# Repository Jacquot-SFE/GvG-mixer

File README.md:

The Gort Vs Goom IEM Mixer.
========================================

Read more about it in [my blog post](https://www.sparkfun.com/news/2352)

Repository Contents
-------------------

* **/Datasheets** - Data sheets for the ICs & other components.
* **/Eagle** - PCB files
* **/Spice** - Simulations of the baxandall and peak hold circuits.
* **/Block-diagram** - Poorly named.  Various vector art, including a block diagram, and panel files.

Documentation
----

Ideas mainly pulled from Doug Self's _Small Signal Audio Design_ book, with other input from datasheets and appnotes from THAT, Jensen, and Nat Semi.

License Information
-------------------

This product is _**open source**_!

Please review the LICENSE.md file for license information.

If you have any questions or concerns on licensing, please contact techsupport@sparkfun.com.

Distributed as-is; no warranty is given.

- Your friends at SparkFun.

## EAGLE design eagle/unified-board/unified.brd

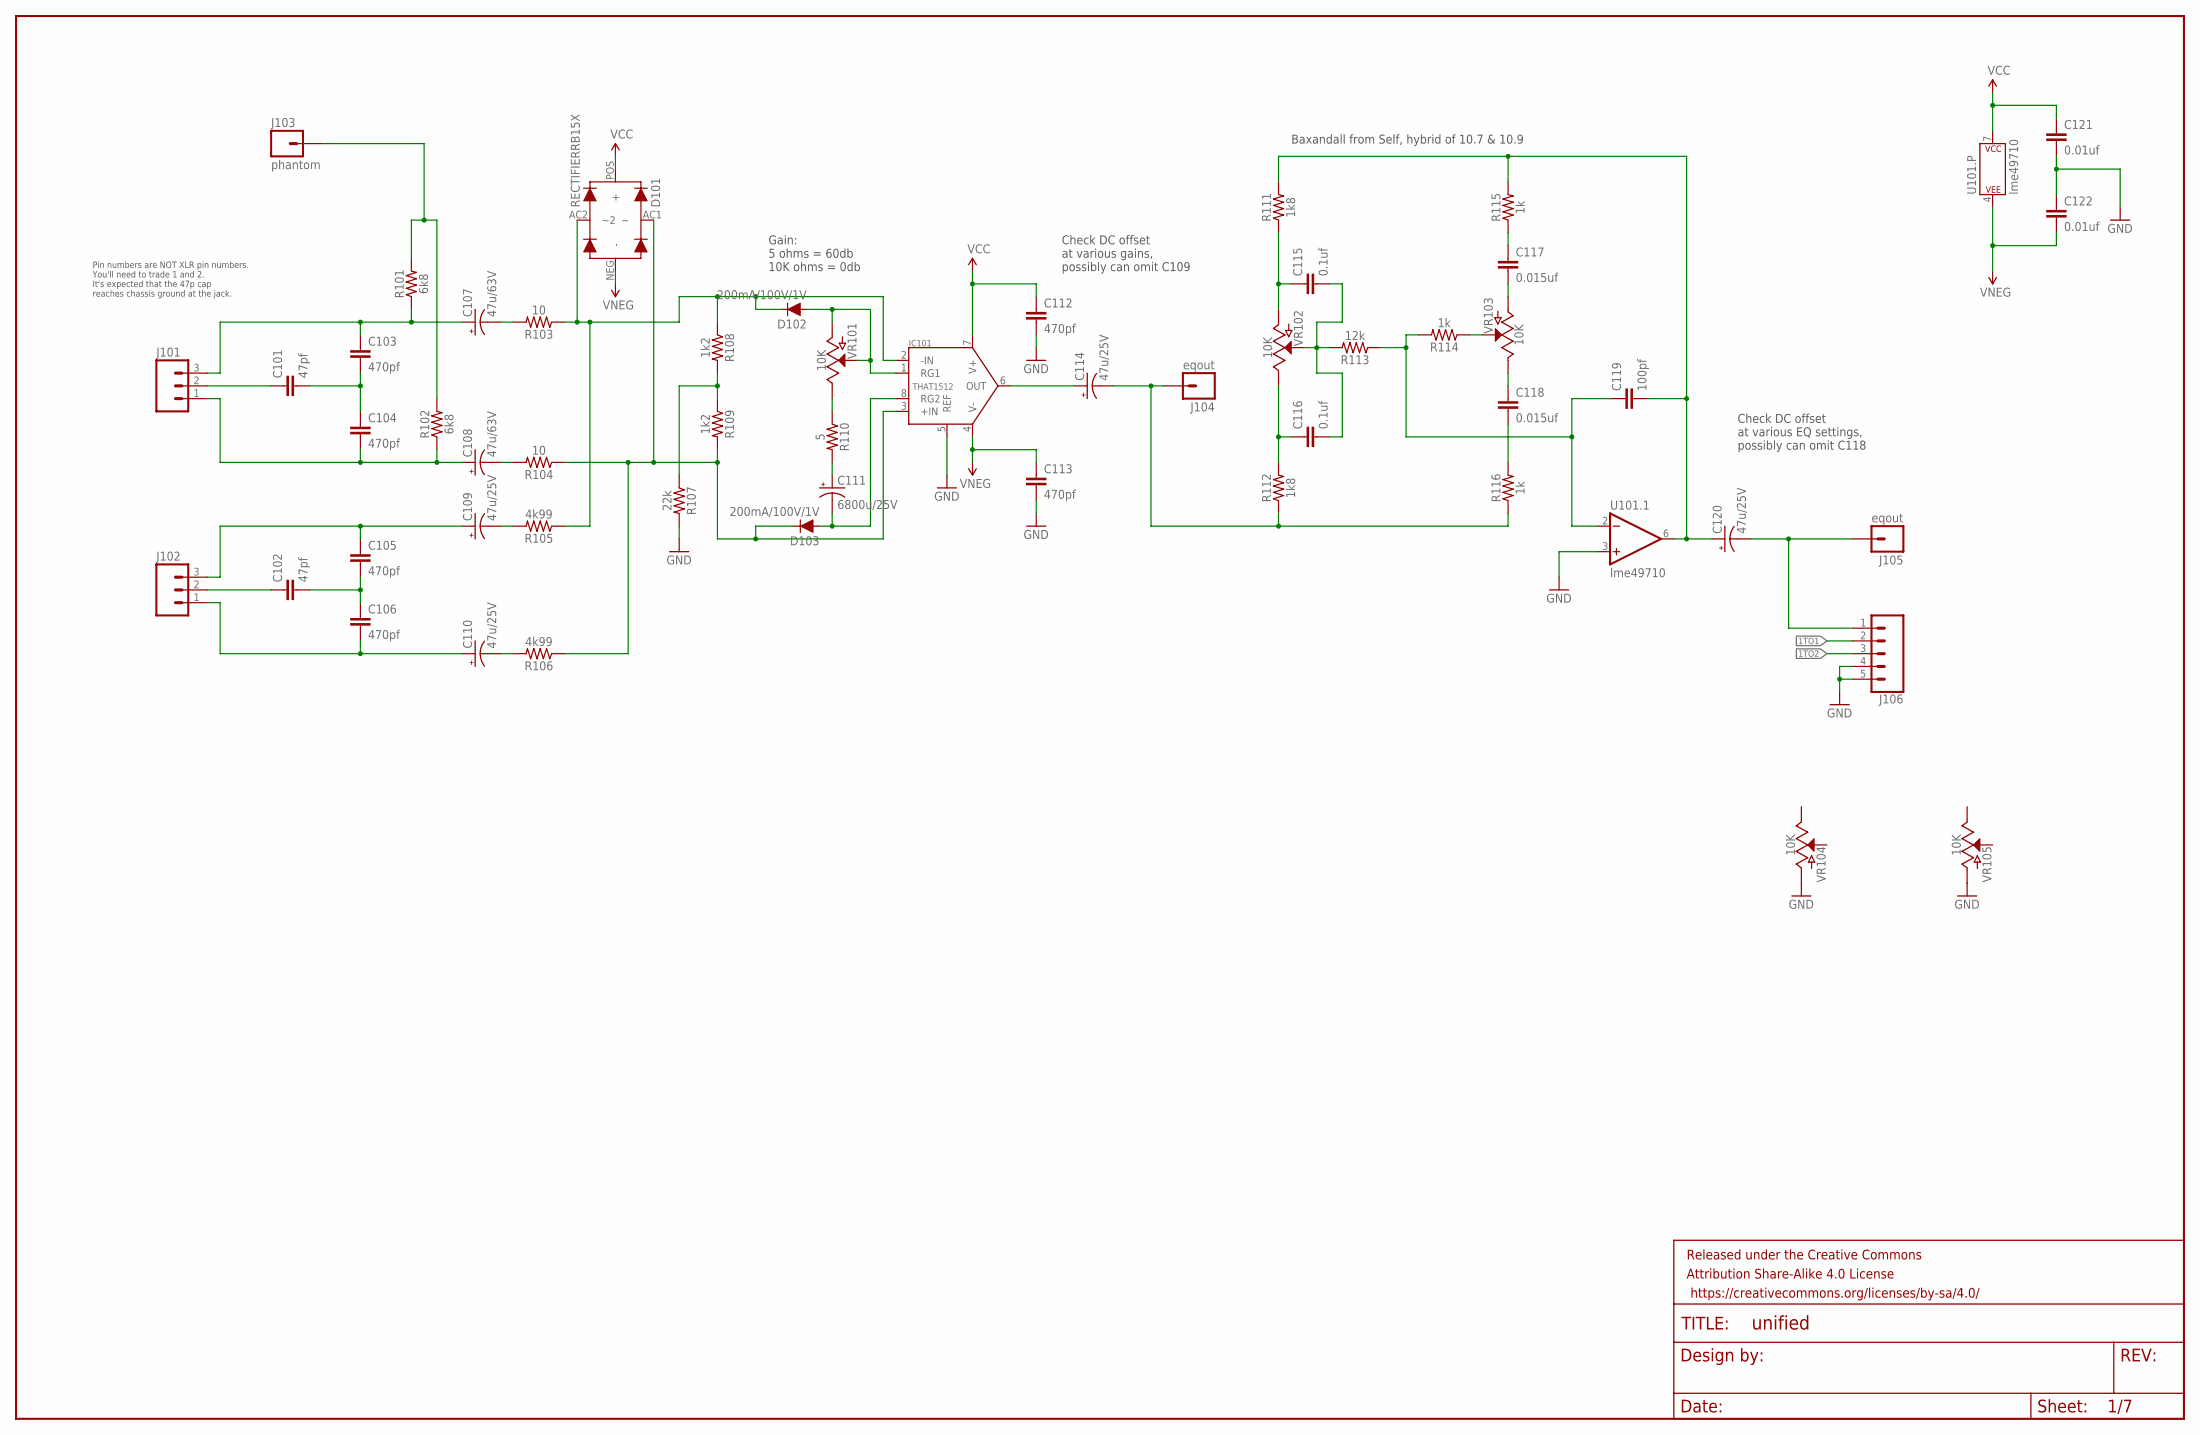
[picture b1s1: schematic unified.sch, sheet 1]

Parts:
C101, C102: 47pf; CAP-KEMET-GM-2.54LS
C103, C104, C105, C106, C112, C113: 470pf; CAP-KEMET-GM-2.54LS
C107, C108: 47u/63V; CAP-PANA-2LS-6DIAM
C109, C110, C114, C120: 47u/25V; CAP-PANA-2LS-5DIAM
C111: 6800u/25V; CAP-PANA-5LS-12.5DIAM
C115, C116: 0.1uf; WIMA-MKS2-2.5X7.2
C117, C118: 0.015uf; WIMA-MKS2-2.5X7.2
C119: 100pf; CAP-KEMET-GM-2.54LS
C121, C122: 0.01uf; WIMA-MKS2-2.5X7.2
D101: RECTIFIERRB15X; SM-RECTIFIER
D102, D103: 200mA/100V/1V; DIODE-1N4148
FRAME101: FRAME-LEDGER; CREATIVE_COMMONS
IC101: THAT1512; DIP08-KIT
J101, J102: M031X03_NO_SILK; 1X03_NO_SILK@1
J103: phantom; 1X01NS-KIT
J104, J105: eqout; 1X01NS-KIT
J106: CONN_05PTH_LONGPADS; 1X05_LONGPADS
R101, R102: 6k8; AXIAL-0.3
R103, R104: 10; AXIAL-0.3
R105, R106: 4k99; AXIAL-0.3
R107: 22k; AXIAL-0.3
R108, R109: 1k2; AXIAL-0.3
R110: 5; AXIAL-0.3
R111, R112: 1k8; AXIAL-0.3
R113: 12k; AXIAL-0.3
R114, R115, R116: 1k; AXIAL-0.3
U101: lme49710; DIP08-KIT
VR101: 10K; ROT-SW-POT
VR102, VR103, VR104, VR105: 10K; ALPHA-RV24AF40-POT

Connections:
1TO1: J106.2; also elsewhere on the board
1TO2: J106.3; also elsewhere on the board
EQ1OUT: C120.NEG (-), J105.1, J106.1
GND: C112.P$2 (2), C113.P$2 (2), C121.P$2 (2), C122.P$1 (1), IC101.5 (REF), J106.4, J106.5, R107.P$2 (2), U101.3 (+IN), VR104.CCW (A), VR105.CCW (A); also elsewhere on the board
L1+: C106.P$2 (2), C110.POS (+), J102.1
L1-: C105.P$1 (1), C109.POS (+), J102.3
L1GND: C102.P$1 (1), J102.2
M1+: C104.P$2 (2), C108.POS (+), J101.1, R102.P$1 (1)
M1-: C103.P$1 (1), C107.POS (+), J101.3, R101.P$1 (1)
M1GND: C101.P$1 (1), J101.2
unnamed: C115.P$1 (1), R111.P$1 (1), VR102.CCW (A)
unnamed: C116.P$1 (1), R112.P$2 (2), VR102.CW (E)
unnamed: C119.P$1 (1), R113.P$1 (1), R114.P$2 (2), U101.2 (-IN)
unnamed: C118.P$2 (2), R116.P$2 (2)
unnamed: C119.P$2 (2), C120.POS (+), R111.P$2 (2), R115.P$2 (2), U101.6 (OUT)
unnamed: R114.P$1 (1), VR103.WIP (S)
unnamed: C118.P$1 (1), VR103.CW (E)
unnamed: C115.P$2 (2), C116.P$2 (2), R113.P$2 (2), VR102.WIP (S)
unnamed: C117.P$2 (2), VR103.CCW (A)
unnamed: C117.P$1 (1), R115.P$1 (1)
unnamed: C111.NEG (-), D103.A, IC101.8 (RG2)
unnamed: C114.POS (+), IC101.6 (OUT)
unnamed: C101.P$2 (2), C103.P$2 (2), C104.P$1 (1)
unnamed: C108.NEG (-), R104.P$2 (2)
unnamed: J103.1, R101.P$2 (2), R102.P$2 (2)
unnamed: C107.NEG (-), R103.P$2 (2)
unnamed: D101.AC2 (~2), D102.C, IC101.2 (-IN), R103.P$1 (1), R105.P$1 (1), R108.P$1 (1)
unnamed: D101.AC1, D103.C, IC101.3 (+IN), R104.P$1 (1), R106.P$1 (1), R109.P$2 (2)
unnamed: R107.P$1 (1), R108.P$2 (2), R109.P$1 (1)
unnamed: D102.A, IC101.1 (RG1), VR101.CCW (A), VR101.WIP (S)
unnamed: R110.P$1 (1), VR101.CW (E)
unnamed: C111.POS (+), R110.P$2 (2)
unnamed: C102.P$2 (2), C105.P$2 (2), C106.P$1 (1)
unnamed: C110.NEG (-), R106.P$2 (2)
unnamed: C109.NEG (-), R105.P$2 (2)
PREOUT: C114.NEG (-), J104.1, R112.P$1 (1), R116.P$1 (1)
VCC: C112.P$1 (1), C121.P$1 (1), D101.POS (+), IC101.7 (V+), U101.7 (P$V+); also elsewhere on the board
VNEG: C113.P$1 (1), C122.P$2 (2), D101.NEG (-), IC101.4 (V-), U101.4 (P$V-); also elsewhere on the board

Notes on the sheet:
Pin numbers are NOT XLR pin numbers. You'll need to trade 1 and 2. It's expected that the 47p cap reaches chassis ground at the jack.
Baxandall from Self, hybrid of 10.7 & 10.9
Gain: 5 ohms = 60db 10K ohms = 0db
Check DC offset at various gains, possibly can omit C109
Check DC offset at various EQ settings, possibly can omit C118

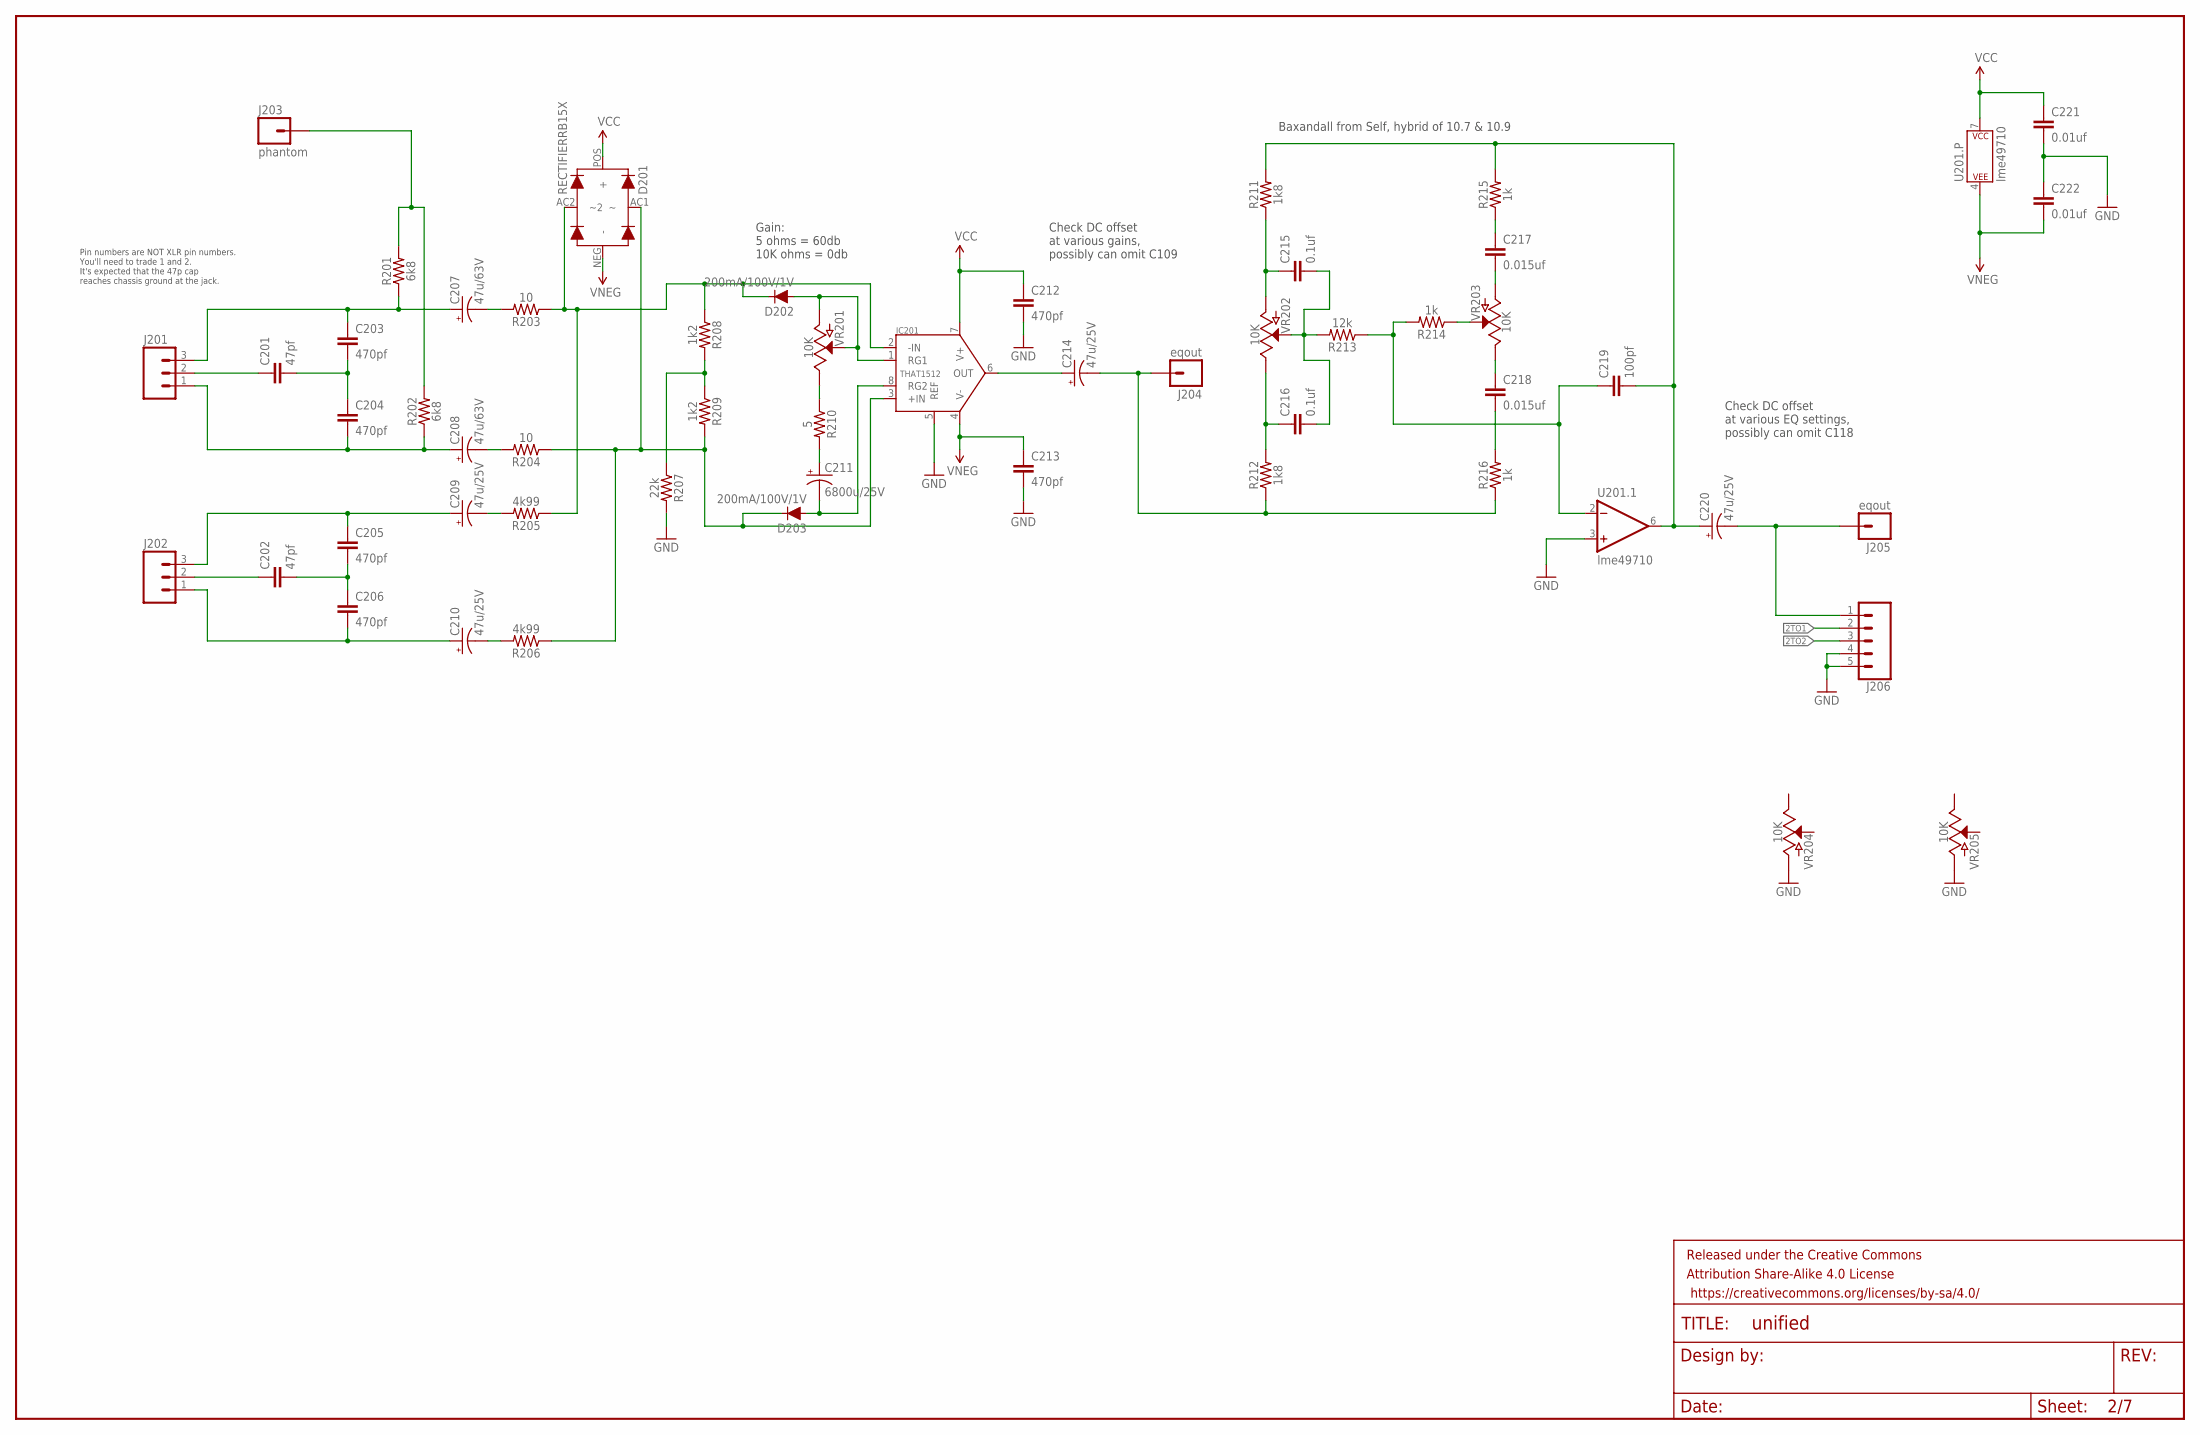
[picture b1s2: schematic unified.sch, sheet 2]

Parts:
C201, C202: 47pf; CAP-KEMET-GM-2.54LS
C203, C204, C205, C206, C212, C213: 470pf; CAP-KEMET-GM-2.54LS
C207, C208: 47u/63V; CAP-PANA-2LS-6DIAM
C209, C210, C214, C220: 47u/25V; CAP-PANA-2LS-5DIAM
C211: 6800u/25V; CAP-PANA-5LS-12.5DIAM
C215, C216: 0.1uf; WIMA-MKS2-2.5X7.2
C217, C218: 0.015uf; WIMA-MKS2-2.5X7.2
C219: 100pf; CAP-KEMET-GM-2.54LS
C221, C222: 0.01uf; WIMA-MKS2-2.5X7.2
D201: RECTIFIERRB15X; SM-RECTIFIER
D202, D203: 200mA/100V/1V; DIODE-1N4148
FRAME201: FRAME-LEDGER; CREATIVE_COMMONS
IC201: THAT1512; DIP08-KIT
J201, J202: M031X03_NO_SILK; 1X03_NO_SILK@1
J203: phantom; 1X01NS-KIT
J204, J205: eqout; 1X01NS-KIT
J206: CONN_05PTH_LONGPADS; 1X05_LONGPADS
R201, R202: 6k8; AXIAL-0.3
R203, R204: 10; AXIAL-0.3
R205, R206: 4k99; AXIAL-0.3
R207: 22k; AXIAL-0.3
R208, R209: 1k2; AXIAL-0.3
R210: 5; AXIAL-0.3
R211, R212: 1k8; AXIAL-0.3
R213: 12k; AXIAL-0.3
R214, R215, R216: 1k; AXIAL-0.3
U201: lme49710; DIP08-KIT
VR201: 10K; ROT-SW-POT
VR202, VR203, VR204, VR205: 10K; ALPHA-RV24AF40-POT

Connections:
2TO1: J206.2; also elsewhere on the board
2TO2: J206.3; also elsewhere on the board
EQ2OUT: C220.NEG (-), J205.1, J206.1
GND: C212.P$2 (2), C213.P$2 (2), C221.P$2 (2), C222.P$1 (1), IC201.5 (REF), J206.4, J206.5, R207.P$2 (2), U201.3 (+IN), VR204.CCW (A), VR205.CCW (A); also elsewhere on the board
unnamed: C214.NEG (-), J204.1, R212.P$1 (1), R216.P$1 (1)
unnamed: C215.P$1 (1), R211.P$1 (1), VR202.CCW (A)
unnamed: C216.P$1 (1), R212.P$2 (2), VR202.CW (E)
unnamed: R214.P$1 (1), VR203.WIP (S)
unnamed: C215.P$2 (2), C216.P$2 (2), R213.P$2 (2), VR202.WIP (S)
unnamed: C218.P$2 (2), R216.P$2 (2)
unnamed: C217.P$1 (1), R215.P$1 (1)
unnamed: C219.P$1 (1), R213.P$1 (1), R214.P$2 (2), U201.2 (-IN)
unnamed: C214.POS (+), IC201.6 (OUT)
unnamed: C201.P$1 (1), J201.2
unnamed: C201.P$2 (2), C203.P$2 (2), C204.P$1 (1)
unnamed: C203.P$1 (1), C207.POS (+), J201.3, R201.P$1 (1)
unnamed: C204.P$2 (2), C208.POS (+), J201.1, R202.P$1 (1)
unnamed: C208.NEG (-), R204.P$2 (2)
unnamed: J203.1, R201.P$2 (2), R202.P$2 (2)
unnamed: C207.NEG (-), R203.P$2 (2)
unnamed: R207.P$1 (1), R208.P$2 (2), R209.P$1 (1)
unnamed: C211.NEG (-), D203.A, IC201.8 (RG2)
unnamed: D202.A, IC201.1 (RG1), VR201.CCW (A), VR201.WIP (S)
unnamed: C218.P$1 (1), VR203.CW (E)
unnamed: C217.P$2 (2), VR203.CCW (A)
unnamed: R210.P$1 (1), VR201.CW (E)
unnamed: C211.POS (+), R210.P$2 (2)
unnamed: C202.P$1 (1), J202.2
unnamed: C202.P$2 (2), C205.P$2 (2), C206.P$1 (1)
unnamed: C205.P$1 (1), C209.POS (+), J202.3
unnamed: C206.P$2 (2), C210.POS (+), J202.1
unnamed: C210.NEG (-), R206.P$2 (2)
unnamed: C209.NEG (-), R205.P$2 (2)
unnamed: D201.AC2 (~2), D202.C, IC201.2 (-IN), R203.P$1 (1), R205.P$1 (1), R208.P$1 (1)
unnamed: D201.AC1, D203.C, IC201.3 (+IN), R204.P$1 (1), R206.P$1 (1), R209.P$2 (2)
unnamed: C219.P$2 (2), C220.POS (+), R211.P$2 (2), R215.P$2 (2), U201.6 (OUT)
VCC: C212.P$1 (1), C221.P$1 (1), D201.POS (+), IC201.7 (V+), U201.7 (P$V+); also elsewhere on the board
VNEG: C213.P$1 (1), C222.P$2 (2), D201.NEG (-), IC201.4 (V-), U201.4 (P$V-); also elsewhere on the board

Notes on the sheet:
Pin numbers are NOT XLR pin numbers. You'll need to trade 1 and 2. It's expected that the 47p cap reaches chassis ground at the jack.
Baxandall from Self, hybrid of 10.7 & 10.9
Gain: 5 ohms = 60db 10K ohms = 0db
Check DC offset at various gains, possibly can omit C109
Check DC offset at various EQ settings, possibly can omit C118

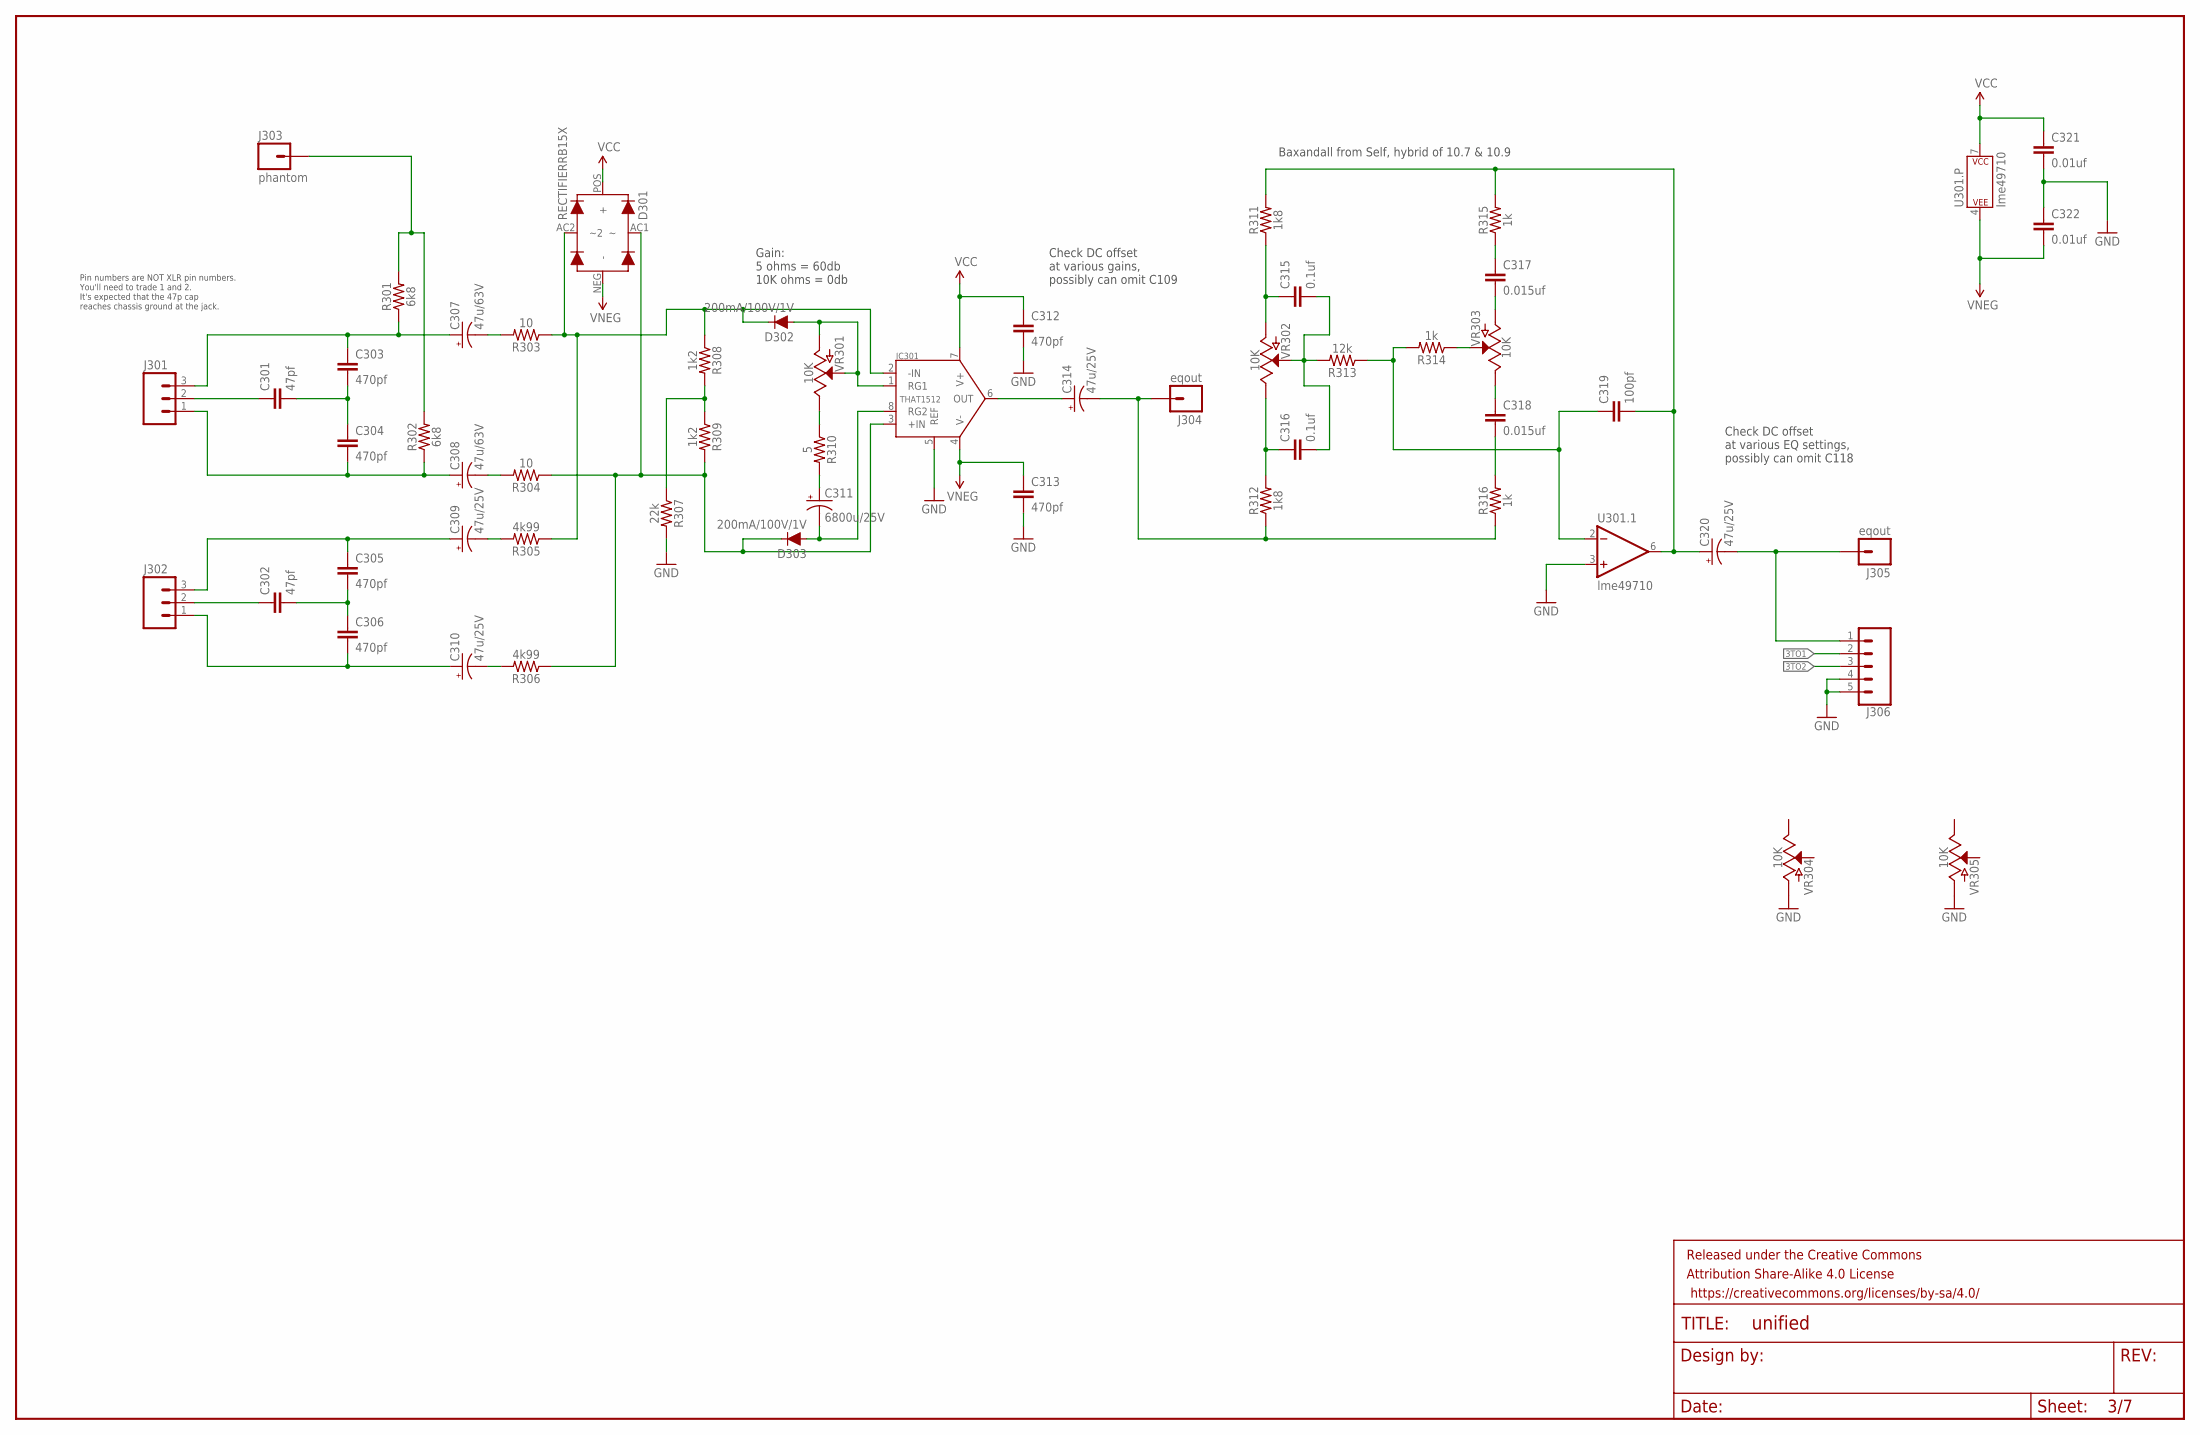
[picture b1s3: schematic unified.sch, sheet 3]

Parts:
C301, C302: 47pf; CAP-KEMET-GM-2.54LS
C303, C304, C305, C306, C312, C313: 470pf; CAP-KEMET-GM-2.54LS
C307, C308: 47u/63V; CAP-PANA-2LS-6DIAM
C309, C310, C314, C320: 47u/25V; CAP-PANA-2LS-5DIAM
C311: 6800u/25V; CAP-PANA-5LS-12.5DIAM
C315, C316: 0.1uf; WIMA-MKS2-2.5X7.2
C317, C318: 0.015uf; WIMA-MKS2-2.5X7.2
C319: 100pf; CAP-KEMET-GM-2.54LS
C321, C322: 0.01uf; WIMA-MKS2-2.5X7.2
D301: RECTIFIERRB15X; SM-RECTIFIER
D302, D303: 200mA/100V/1V; DIODE-1N4148
FRAME301: FRAME-LEDGER; CREATIVE_COMMONS
IC301: THAT1512; DIP08-KIT
J301, J302: M031X03_NO_SILK; 1X03_NO_SILK@1
J303: phantom; 1X01NS-KIT
J304, J305: eqout; 1X01NS-KIT
J306: CONN_05PTH_LONGPADS; 1X05_LONGPADS
R301, R302: 6k8; AXIAL-0.3
R303, R304: 10; AXIAL-0.3
R305, R306: 4k99; AXIAL-0.3
R307: 22k; AXIAL-0.3
R308, R309: 1k2; AXIAL-0.3
R310: 5; AXIAL-0.3
R311, R312: 1k8; AXIAL-0.3
R313: 12k; AXIAL-0.3
R314, R315, R316: 1k; AXIAL-0.3
U301: lme49710; DIP08-KIT
VR301: 10K; ROT-SW-POT
VR302, VR303, VR304, VR305: 10K; ALPHA-RV24AF40-POT

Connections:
3TO1: J306.2; also elsewhere on the board
3TO2: J306.3; also elsewhere on the board
EQ3OUT: C320.NEG (-), J305.1, J306.1
GND: C312.P$2 (2), C313.P$2 (2), C321.P$2 (2), C322.P$1 (1), IC301.5 (REF), J306.4, J306.5, R307.P$2 (2), U301.3 (+IN), VR304.CCW (A), VR305.CCW (A); also elsewhere on the board
unnamed: C314.NEG (-), J304.1, R312.P$1 (1), R316.P$1 (1)
unnamed: C315.P$1 (1), R311.P$1 (1), VR302.CCW (A)
unnamed: C316.P$1 (1), R312.P$2 (2), VR302.CW (E)
unnamed: R314.P$1 (1), VR303.WIP (S)
unnamed: C315.P$2 (2), C316.P$2 (2), R313.P$2 (2), VR302.WIP (S)
unnamed: C318.P$2 (2), R316.P$2 (2)
unnamed: C317.P$1 (1), R315.P$1 (1)
unnamed: C319.P$1 (1), R313.P$1 (1), R314.P$2 (2), U301.2 (-IN)
unnamed: C314.POS (+), IC301.6 (OUT)
unnamed: C301.P$1 (1), J301.2
unnamed: C301.P$2 (2), C303.P$2 (2), C304.P$1 (1)
unnamed: C303.P$1 (1), C307.POS (+), J301.3, R301.P$1 (1)
unnamed: C304.P$2 (2), C308.POS (+), J301.1, R302.P$1 (1)
unnamed: C308.NEG (-), R304.P$2 (2)
unnamed: J303.1, R301.P$2 (2), R302.P$2 (2)
unnamed: C307.NEG (-), R303.P$2 (2)
unnamed: R307.P$1 (1), R308.P$2 (2), R309.P$1 (1)
unnamed: C311.NEG (-), D303.A, IC301.8 (RG2)
unnamed: D302.A, IC301.1 (RG1), VR301.CCW (A), VR301.WIP (S)
unnamed: C318.P$1 (1), VR303.CW (E)
unnamed: C317.P$2 (2), VR303.CCW (A)
unnamed: R310.P$1 (1), VR301.CW (E)
unnamed: C311.POS (+), R310.P$2 (2)
unnamed: C302.P$1 (1), J302.2
unnamed: C302.P$2 (2), C305.P$2 (2), C306.P$1 (1)
unnamed: C305.P$1 (1), C309.POS (+), J302.3
unnamed: C306.P$2 (2), C310.POS (+), J302.1
unnamed: C310.NEG (-), R306.P$2 (2)
unnamed: C309.NEG (-), R305.P$2 (2)
unnamed: D301.AC2 (~2), D302.C, IC301.2 (-IN), R303.P$1 (1), R305.P$1 (1), R308.P$1 (1)
unnamed: D301.AC1, D303.C, IC301.3 (+IN), R304.P$1 (1), R306.P$1 (1), R309.P$2 (2)
unnamed: C319.P$2 (2), C320.POS (+), R311.P$2 (2), R315.P$2 (2), U301.6 (OUT)
VCC: C312.P$1 (1), C321.P$1 (1), D301.POS (+), IC301.7 (V+), U301.7 (P$V+); also elsewhere on the board
VNEG: C313.P$1 (1), C322.P$2 (2), D301.NEG (-), IC301.4 (V-), U301.4 (P$V-); also elsewhere on the board

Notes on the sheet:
Pin numbers are NOT XLR pin numbers. You'll need to trade 1 and 2. It's expected that the 47p cap reaches chassis ground at the jack.
Baxandall from Self, hybrid of 10.7 & 10.9
Gain: 5 ohms = 60db 10K ohms = 0db
Check DC offset at various gains, possibly can omit C109
Check DC offset at various EQ settings, possibly can omit C118

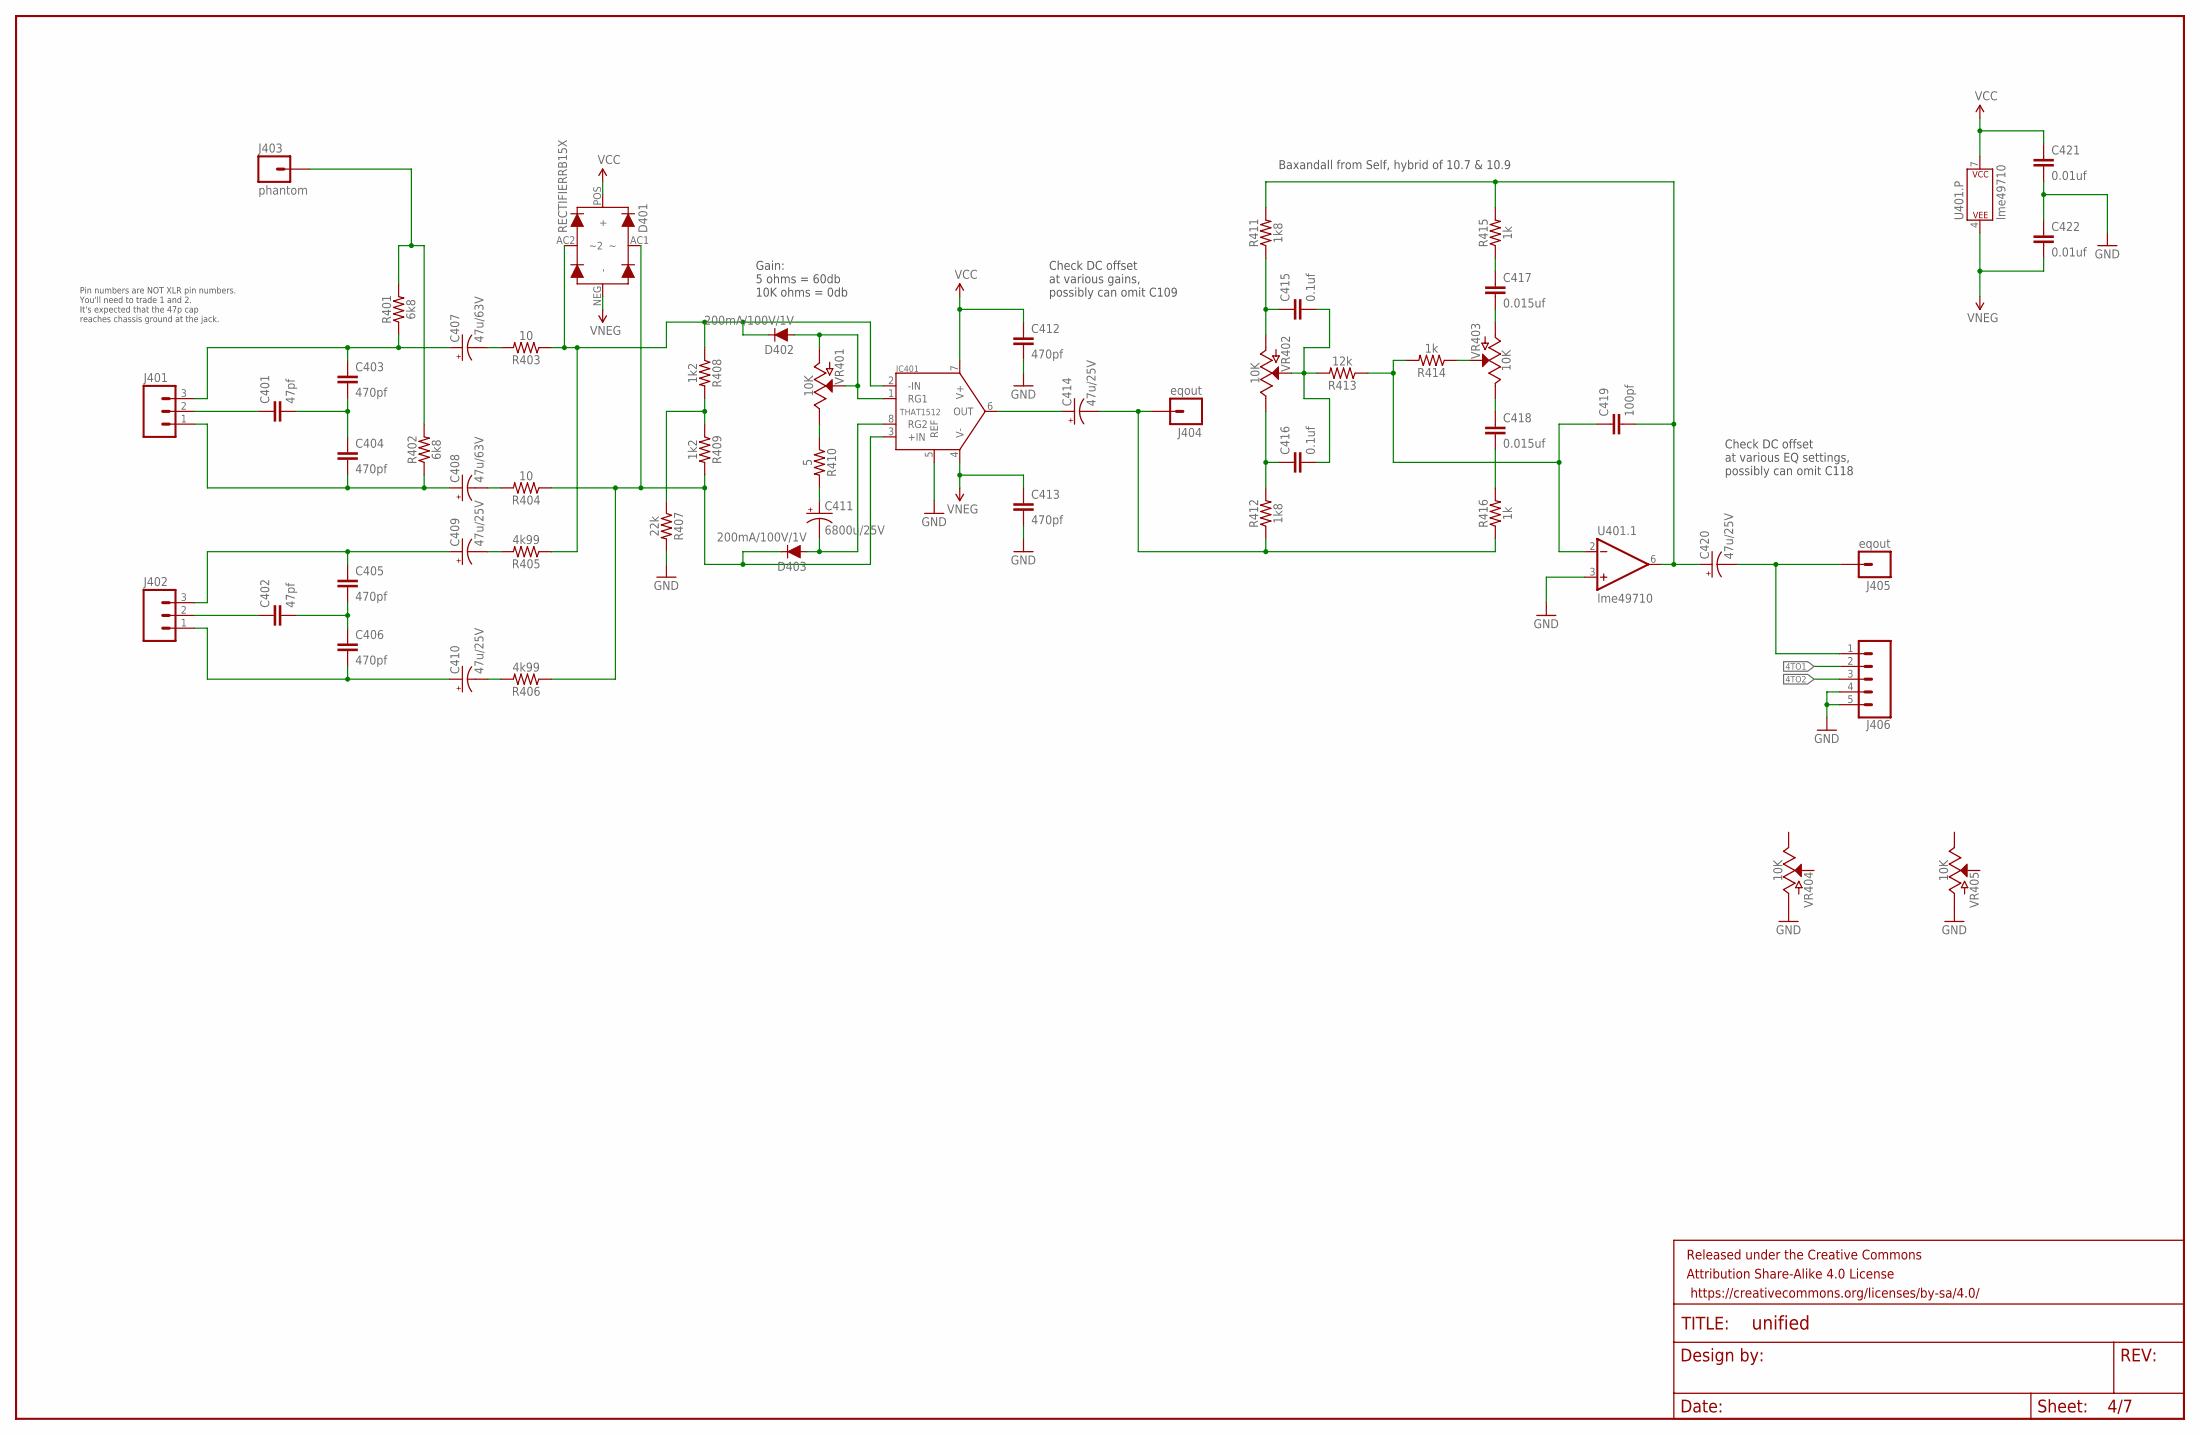
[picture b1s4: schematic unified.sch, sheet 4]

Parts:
C401, C402: 47pf; CAP-KEMET-GM-2.54LS
C403, C404, C405, C406, C412, C413: 470pf; CAP-KEMET-GM-2.54LS
C407, C408: 47u/63V; CAP-PANA-2LS-6DIAM
C409, C410, C414, C420: 47u/25V; CAP-PANA-2LS-5DIAM
C411: 6800u/25V; CAP-PANA-5LS-12.5DIAM
C415, C416: 0.1uf; WIMA-MKS2-2.5X7.2
C417, C418: 0.015uf; WIMA-MKS2-2.5X7.2
C419: 100pf; CAP-KEMET-GM-2.54LS
C421, C422: 0.01uf; WIMA-MKS2-2.5X7.2
D401: RECTIFIERRB15X; SM-RECTIFIER
D402, D403: 200mA/100V/1V; DIODE-1N4148
FRAME401: FRAME-LEDGER; CREATIVE_COMMONS
IC401: THAT1512; DIP08-KIT
J401, J402: M031X03_NO_SILK; 1X03_NO_SILK@1
J403: phantom; 1X01NS-KIT
J404, J405: eqout; 1X01NS-KIT
J406: CONN_05PTH_LONGPADS; 1X05_LONGPADS
R401, R402: 6k8; AXIAL-0.3
R403, R404: 10; AXIAL-0.3
R405, R406: 4k99; AXIAL-0.3
R407: 22k; AXIAL-0.3
R408, R409: 1k2; AXIAL-0.3
R410: 5; AXIAL-0.3
R411, R412: 1k8; AXIAL-0.3
R413: 12k; AXIAL-0.3
R414, R415, R416: 1k; AXIAL-0.3
U401: lme49710; DIP08-KIT
VR401: 10K; ROT-SW-POT
VR402, VR403, VR404, VR405: 10K; ALPHA-RV24AF40-POT

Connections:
4TO1: J406.2; also elsewhere on the board
4TO2: J406.3; also elsewhere on the board
EQ4OUT: C420.NEG (-), J405.1, J406.1
GND: C412.P$2 (2), C413.P$2 (2), C421.P$2 (2), C422.P$1 (1), IC401.5 (REF), J406.4, J406.5, R407.P$2 (2), U401.3 (+IN), VR404.CCW (A), VR405.CCW (A); also elsewhere on the board
unnamed: C414.NEG (-), J404.1, R412.P$1 (1), R416.P$1 (1)
unnamed: C415.P$1 (1), R411.P$1 (1), VR402.CCW (A)
unnamed: C416.P$1 (1), R412.P$2 (2), VR402.CW (E)
unnamed: R414.P$1 (1), VR403.WIP (S)
unnamed: C415.P$2 (2), C416.P$2 (2), R413.P$2 (2), VR402.WIP (S)
unnamed: C418.P$2 (2), R416.P$2 (2)
unnamed: C417.P$1 (1), R415.P$1 (1)
unnamed: C419.P$1 (1), R413.P$1 (1), R414.P$2 (2), U401.2 (-IN)
unnamed: C414.POS (+), IC401.6 (OUT)
unnamed: C401.P$1 (1), J401.2
unnamed: C401.P$2 (2), C403.P$2 (2), C404.P$1 (1)
unnamed: C403.P$1 (1), C407.POS (+), J401.3, R401.P$1 (1)
unnamed: C404.P$2 (2), C408.POS (+), J401.1, R402.P$1 (1)
unnamed: C408.NEG (-), R404.P$2 (2)
unnamed: J403.1, R401.P$2 (2), R402.P$2 (2)
unnamed: C407.NEG (-), R403.P$2 (2)
unnamed: R407.P$1 (1), R408.P$2 (2), R409.P$1 (1)
unnamed: C411.NEG (-), D403.A, IC401.8 (RG2)
unnamed: D402.A, IC401.1 (RG1), VR401.CCW (A), VR401.WIP (S)
unnamed: C418.P$1 (1), VR403.CW (E)
unnamed: C417.P$2 (2), VR403.CCW (A)
unnamed: R410.P$1 (1), VR401.CW (E)
unnamed: C411.POS (+), R410.P$2 (2)
unnamed: C402.P$1 (1), J402.2
unnamed: C402.P$2 (2), C405.P$2 (2), C406.P$1 (1)
unnamed: C405.P$1 (1), C409.POS (+), J402.3
unnamed: C406.P$2 (2), C410.POS (+), J402.1
unnamed: C410.NEG (-), R406.P$2 (2)
unnamed: C409.NEG (-), R405.P$2 (2)
unnamed: D401.AC2 (~2), D402.C, IC401.2 (-IN), R403.P$1 (1), R405.P$1 (1), R408.P$1 (1)
unnamed: D401.AC1, D403.C, IC401.3 (+IN), R404.P$1 (1), R406.P$1 (1), R409.P$2 (2)
unnamed: C419.P$2 (2), C420.POS (+), R411.P$2 (2), R415.P$2 (2), U401.6 (OUT)
VCC: C412.P$1 (1), C421.P$1 (1), D401.POS (+), IC401.7 (V+), U401.7 (P$V+); also elsewhere on the board
VNEG: C413.P$1 (1), C422.P$2 (2), D401.NEG (-), IC401.4 (V-), U401.4 (P$V-); also elsewhere on the board

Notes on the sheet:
Pin numbers are NOT XLR pin numbers. You'll need to trade 1 and 2. It's expected that the 47p cap reaches chassis ground at the jack.
Baxandall from Self, hybrid of 10.7 & 10.9
Gain: 5 ohms = 60db 10K ohms = 0db
Check DC offset at various gains, possibly can omit C109
Check DC offset at various EQ settings, possibly can omit C118

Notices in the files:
parts and their libraries:
SparkFun-Capacitors: Licensing: Creative Commons ShareAlike 4.0 International - https://creativecommons.org/licenses/by-sa/4.0
SparkFun-Aesthetics: Released under the Creative Commons Attribution Share-Alike 4.0 License
SparkFun-Aesthetics: https://creativecommons.org/licenses/by-sa/4.0
